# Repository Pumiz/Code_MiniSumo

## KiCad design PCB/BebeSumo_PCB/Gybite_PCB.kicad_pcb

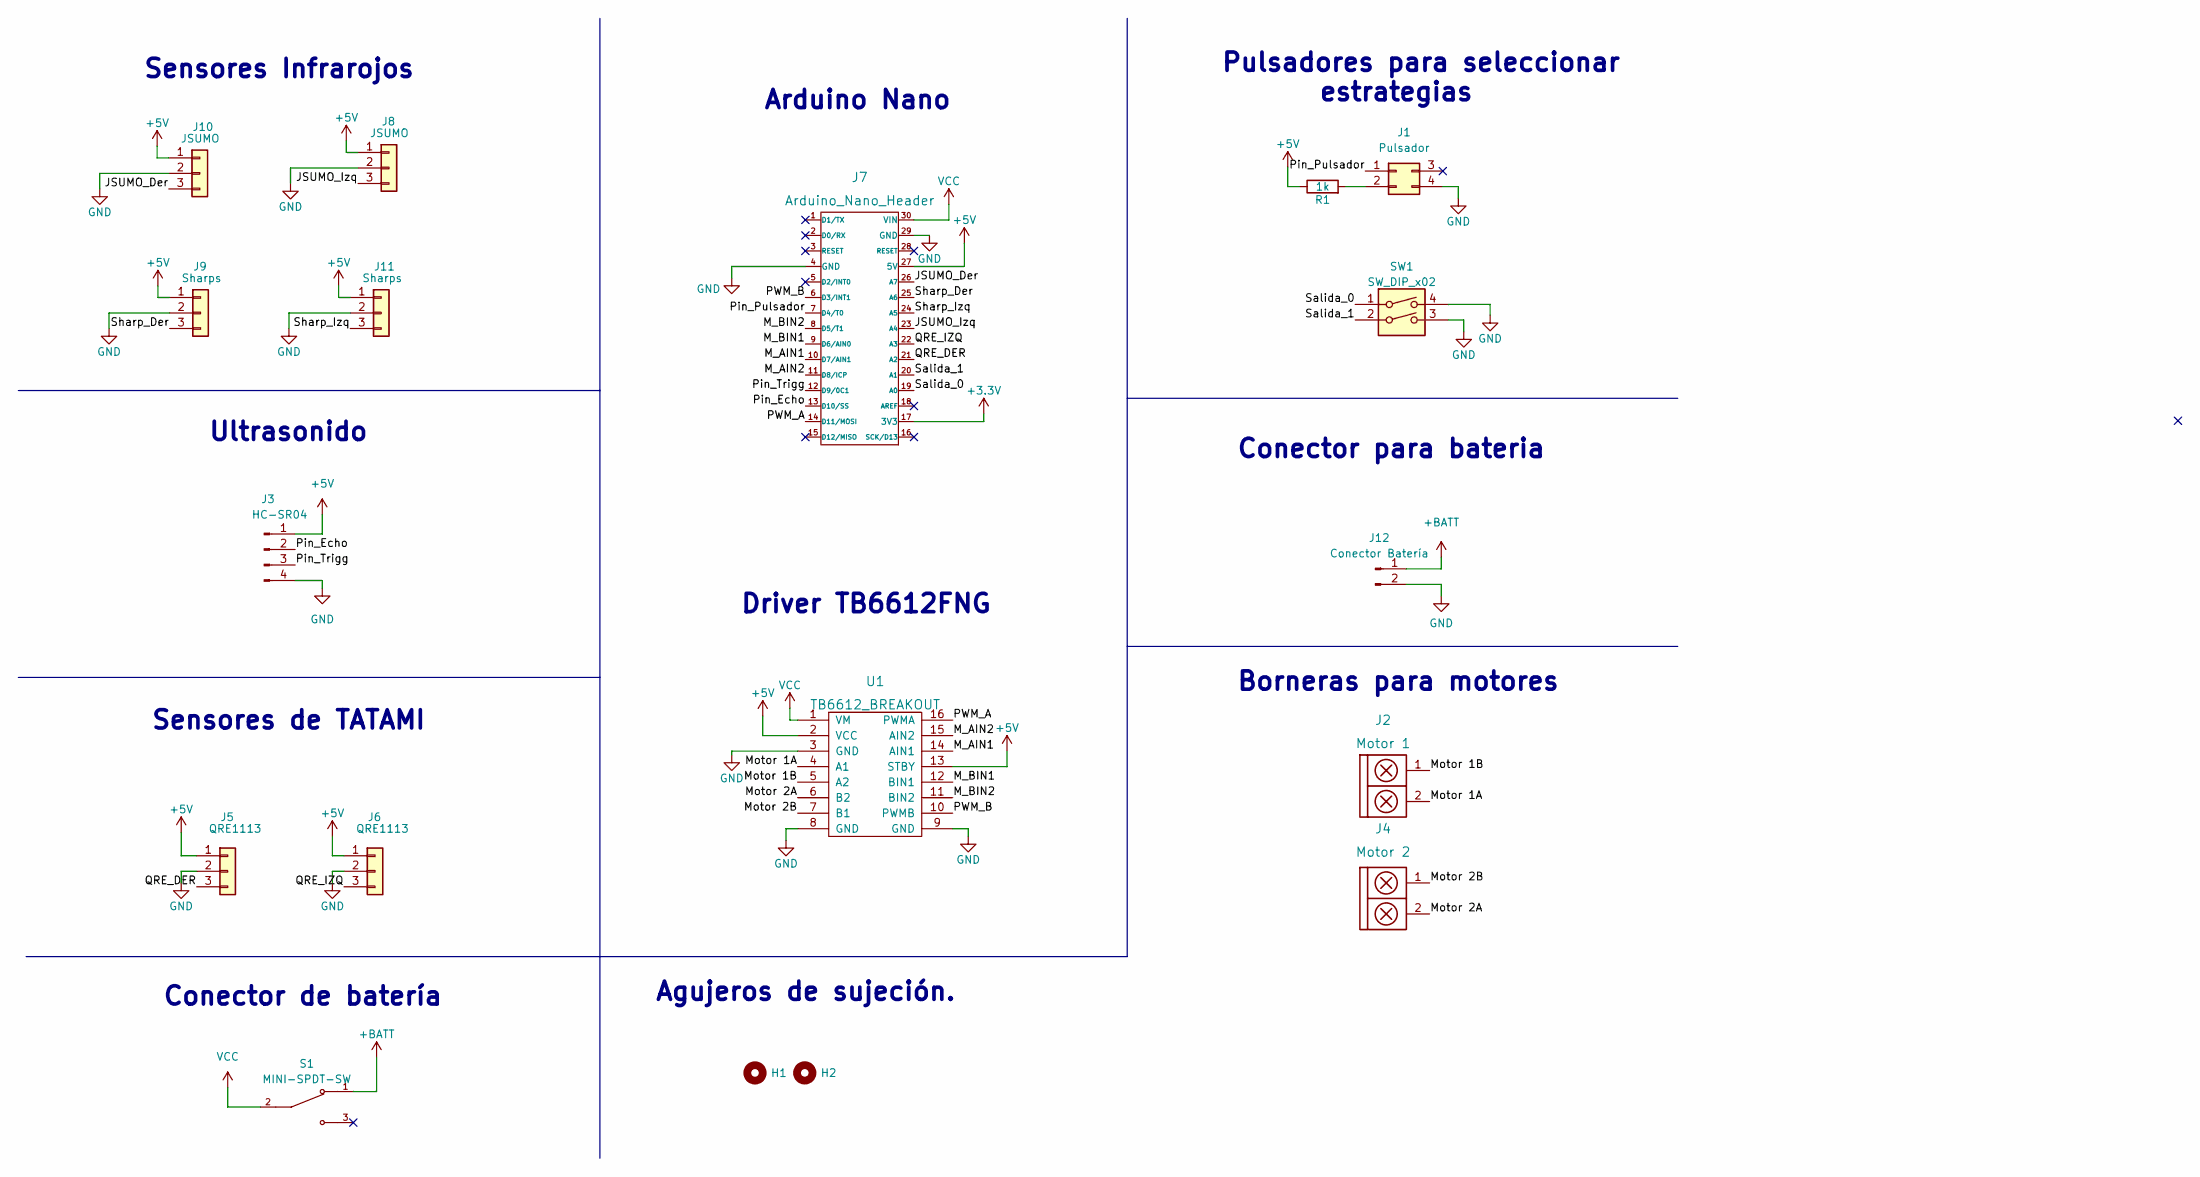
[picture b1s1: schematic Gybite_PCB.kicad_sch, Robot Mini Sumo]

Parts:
H1, H2: Mounting_Hole; hole_2mm
J1: Pulsador; Pulsador_TH_4
J2: Motor 1; BORNERA2_AZUL
J3: HC-SR04; JST_EH_B4B-EH-A_1x04_P2.50mm_Vertical
J4: Motor 2; BORNERA2_AZUL
J5, J6: QRE1113; JST_EH_B3B-EH-A_1x03_P2.50mm_Vertical
J7: Arduino_Nano_Header; arduino_nano_header
J8, J10: JSUMO; JST_EH_B3B-EH-A_1x03_P2.50mm_Vertical
J9, J11: Sharps; JST_EH_B3B-EH-A_1x03_P2.50mm_Vertical
J12: Conector Batería; JST_EH_B2B-EH-A_1x02_P2.50mm_Vertical
R1: 1k; RES0.3
S1: MINI-SPDT-SW; Switch_SS12F44_123; PARTREV C
SW1: SW_DIP_x02; SW_DIP_SPSTx02_Slide_9.78x7.26mm_W7.62mm_P2.54mm
U1: TB6612_BREAKOUT; TB6612_Breakout

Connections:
+3V3: J7.17 (3V3)
+5V: J3.1, J5.1, J6.1, J7.27 (5V), J8.1, J9.1, J10.1, J11.1, R1.1, U1.2 (VCC), U1.13 (STBY)
+BATT: J12.1, S1.1
/JSUMO_Der: J7.26 (A7), J10.3
/JSUMO_Izq: J7.23 (A4), J8.3
/M_AIN1: J7.10 (D7/AIN1), U1.14 (AIN1)
/M_AIN2: J7.11 (D8/ICP), U1.15 (AIN2)
/M_BIN1: J7.9 (D6/AIN0), U1.12 (BIN1)
/M_BIN2: J7.8 (D5/T1), U1.11 (BIN2)
/Motor 1A: J2.2, U1.4 (A1)
/Motor 1B: J2.1, U1.5 (A2)
/Motor 2A: J4.2, U1.6 (B2)
/Motor 2B: J4.1, U1.7 (B1)
/PWM_A: J7.14 (D11/MOSI), U1.16 (PWMA)
/PWM_B: J7.6 (D3/INT1), U1.10 (PWMB)
/Pin_Echo: J3.2, J7.13 (D10/SS)
/Pin_Pulsador: J1.1, J7.7 (D4/T0)
/Pin_Trigg: J3.3, J7.12 (D9/0C1)
/QRE_DER: J5.3, J7.21 (A2)
/QRE_IZQ: J6.3, J7.22 (A3)
/Salida_0: J7.19 (A0), SW1.1
/Salida_1: J7.20 (A1), SW1.2
/Sharp_Der: J7.25 (A6), J9.3
/Sharp_Izq: J7.24 (A5), J11.3
GND: J1.4, J3.4, J5.2, J6.2, J7.4 (GND), J7.29 (GND), J8.2, J9.2, J10.2, J11.2, J12.2, SW1.3, SW1.4, U1.3 (GND), U1.8 (GND), U1.9 (GND)
unnamed: J1.2, R1.2
VCC: J7.30 (VIN), S1.2, U1.1 (VM)

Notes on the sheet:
Borneras para motores
Driver TB6612FNG
Sensores Infrarojos
Conector de batería
Sensores de TATAMI
Arduino Nano
Agujeros de sujeción.
Pulsadores para seleccionar estrategias
Conector para bateria
Ultrasonido

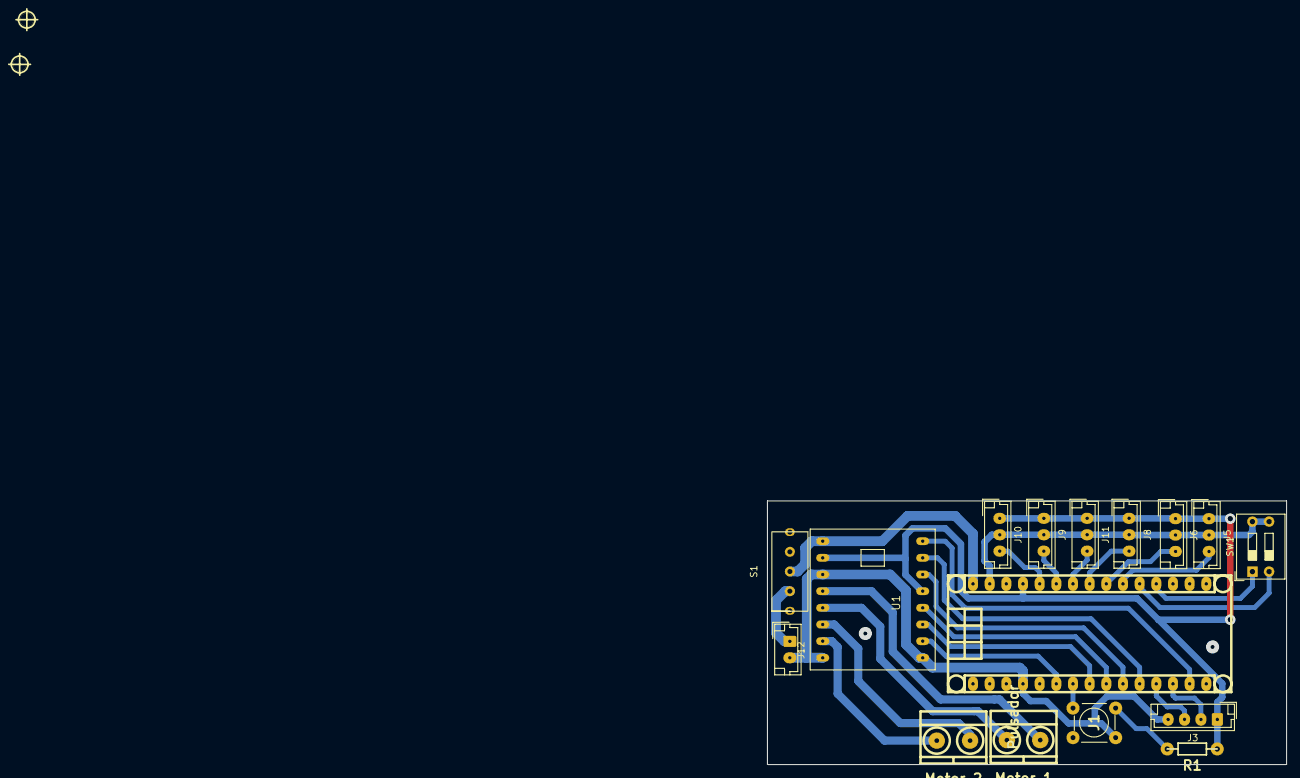
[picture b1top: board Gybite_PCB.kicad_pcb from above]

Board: 2 copper layers, 79.1 x 40.2 mm, 18 parts (0 on the bottom side), 26 nets.

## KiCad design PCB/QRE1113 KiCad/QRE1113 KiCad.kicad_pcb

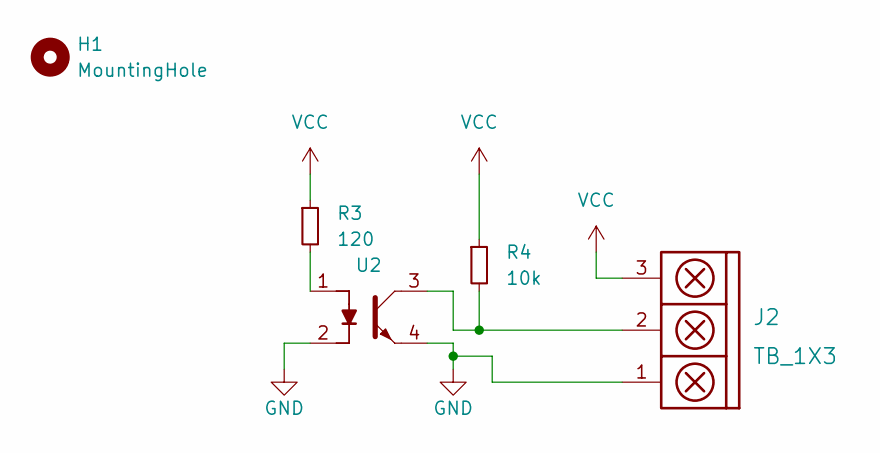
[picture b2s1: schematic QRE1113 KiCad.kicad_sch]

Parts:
H1: MountingHole; MountingHole_3.2mm_M3_DIN965_Pad
J2: TB_1X3; Pin_Strip_3
R3: 120; R_1206
R4: 10k; R_1206
U2: QRE1113; QRE1113GR

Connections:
GND: J2.1, U2.2, U2.4
unnamed: J2.2, R4.2, U2.3
unnamed: R3.2, U2.1
VCC: J2.3, R3.1, R4.1

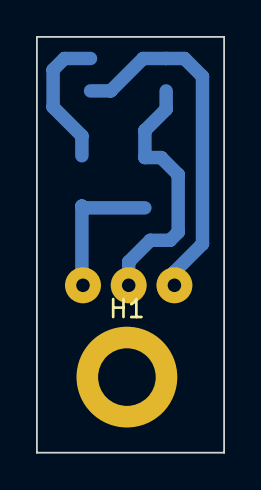
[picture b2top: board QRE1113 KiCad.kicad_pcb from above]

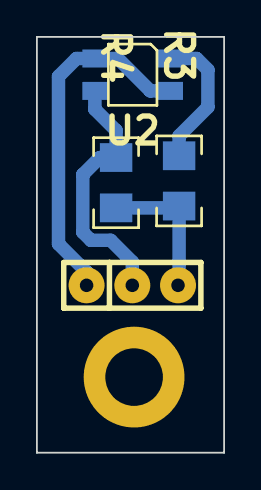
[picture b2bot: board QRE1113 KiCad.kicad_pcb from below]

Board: 2 copper layers, 10.4 x 23.1 mm, 5 parts (4 on the bottom side), 4 nets.

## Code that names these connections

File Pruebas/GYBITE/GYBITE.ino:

//--------------FUNCIONES GLOBALES---------------
#define DEBUG 1  //con DEBUG en 0 no muestra SerialPrint´s  
#define DEBUG_PULSADOR 1
#define DEBUG_CASOS 0
#define ON HIGH
#define OFF LOW
#include "Define.h"
#include "OnlyWrite.h"


//-------------------MOTORES---------------------
int Pines_Motor[6] = {
  MOTOR_DER_1,
  MOTOR_DER_2,
  MOTOR_IZQ_1,
  MOTOR_IZQ_2,
  PWM_MOTOR_DER,
  PWM_MOTOR_IZQ
};

//-------------------PULSADOR-------------------
enum Modo {
  Limpiar_Ruedas,
  Matar_Derecha,
  Te_Espero,
  Matar
};

String ESTADOS[] = {
  "Limpiar_Ruedas",
  "Matar_Derecha",
  "Te_Espero",
  "Matar",
};

//------------------ULTRASONIDO------------------
// MARRON:  VCC
// AZUL:    TRIG
// VERDE:   ECHO
// NEGRO:   GND

long Tiempo;
long Distancia;

//--------------------SHARP`S--------------------
// ROSA:     SEÑAL
// AMARILLO: GND
// CELESTE:  VCC

unsigned int SHARP_der = 0;
unsigned int SHARP_izq = 0;
unsigned int RivalSharp = 60;  // 60cm, basicamente al otra punta de tatami.

int Pines_Sharps[2] = {
  PIN_SHARP_DER,
  PIN_SHARP_IZQ,
};

//----------------------JSUMO--------------------
// ROSA:     SEÑAL
// AMARILLO: GND
// CELESTE:  VCC

int sensor = 0;

unsigned int JSUMO_der = 0;
unsigned int JSUMO_izq = 0;
unsigned int Rival = 500;  // Si no ve nada tira 0 o tende a valores muy cercados. Ej: 17
// Si detecta algo, NO IMPORTA LA DISTANCIA tende a arriba de los 800.

int Pines_JSUMO[2] = {
  PIN_JSUMO_F_D,
  PIN_JSUMO_F_I,
};

//---------------------QRE1113--------------------
//Próximamente.


//--------------------FUNCIONES-------------------

void AsignacionPines() {
  for (int idx = 0; idx < 6; idx++) {
    int pin = Pines_Motor[idx];
    pinMode(pin, OUTPUT);
  }

  for (int idx = 0; idx < 2; idx++) {
    int pin = Pines_Sharps[idx];
    pinMode(pin, INPUT);
  }

  for (int idx = 0; idx < 2; idx++) {
    int pin = Pines_JSUMO[idx];
    pinMode(pin, INPUT);
  }

  pinMode(PIN_PULSADOR, INPUT);
  pinMode(PIN_LED, OUTPUT);
  pinMode(PIN_ECHO, INPUT);
  pinMode(PIN_TRIG, OUTPUT);
  digitalWrite(PIN_TRIG, LOW);
}

void EnviarPulso() {
  digitalWrite(PIN_TRIG, HIGH);
  delayMicroseconds(10);
  digitalWrite(PIN_TRIG, LOW);
  Tiempo = pulseIn(PIN_ECHO, HIGH);
  Distancia = Tiempo / 58;  // El tiempo dividido 58 te da la distancia en centìmetros.
}

void SensarSensores() {

  JSUMO_izq = analogRead(PIN_JSUMO_F_I);
  JSUMO_der = analogRead(PIN_JSUMO_F_D);
  QREder = analogRead(QRE_DERECHO);
  QREizq = analogRead(QRE_IZQUIERDO);
}

void Menu() {
  while (!digitalRead(PIN_PULSADOR)) {
    tiempo++;
    Serial.println(tiempo);
  }
  if (tiempo > tiempo_min && tiempo < tiempo_max) {
    //cambiar estrategia
    caso++;
    tiempo = 0;
    if(DEBUG_PULSADOR)Serial.print("Estas en: ");
    if(DEBUG_PULSADOR)Serial.println(ESTADOS[caso]);
    pantalla = true;
  } else if (tiempo > tiempo_max && pantalla == true) {
    //entrar en el modo
    if(DEBUG_PULSADOR)Serial.print("En ruedo: ");
    if(DEBUG_PULSADOR)Serial.println(ESTADOS[caso]);
    digitalWrite(PIN_LED, HIGH);
    delay(5000);
    digitalWrite(PIN_LED, LOW);
    pantalla = false;
    Mode = true;
    tiempo = 0;
  }
}
#include "Estrategias.h"
//--------------------SETUP-------------------
void setup() {
  Serial.begin(9600);
  AsignacionPines();
  if(DEBUG_PULSADOR)Serial.print("Estas en: ");
  if(DEBUG_PULSADOR)Serial.println(ESTADOS[caso]);
  EncenderLed(); //esto es para saber cuando el arduino termino de leer las líneras anteriores a estas.
}

//--------------------LOOP-------------------
void loop() {

  Menu();


  switch (caso) {
    case Limpiar_Ruedas:
      if (Mode == true) {
        if(DEBUG_CASOS)Serial.println("EN RUEDO Limpiar Ruedas");
        LimpiarRuedas();
      }
      break;
    case Matar_Derecha:
      if (Mode == true) {
        if(DEBUG_CASOS)Serial.println("EN RUEDO Matar Derecha");
        MATARDERECHA();
      }
      break;
    case Te_Espero:
      if (Mode == true) {
        if(DEBUG_CASOS)Serial.println("EN RUEDO Te Espero...");
        TeEspero();
      }
      break;
    case Matar:
      if (Mode == true) {
        if(DEBUG_CASOS)Serial.println("EN RUEDO Matar");
        MATAR();
      }
      break;
  }
}

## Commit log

2022-09-07 Subo el codigo de FRAMAR
2022-09-14 Agregue el código del pulsador final del July
2022-09-14 Agregue el codigo base de Gybite
2022-09-22 Update Gybite_Code.ino
    Agregue todos los pines.
2022-09-27 Agregue el código del pulsador
2022-10-22 Update Gybite_Code.ino
    Actualice el codigo de Gybite para la fecha de La Salle. Estrategia uno funciona.
2022-11-02 Cambie el pulsador al pin digital.
2022-11-03 Agregue el codigod e Gybite optimizado
2022-11-09 Subo el codigo base con todas sus librerias nuevas.
2022-11-29 Agregue el nuevo pulsador y meti todas las librerias juntas.
2023-02-07 Nuevo codigo BebeSumo 2023
2023-04-12 Se agrego la carpeta con el PCB de la placa y los QRE
2023-04-14 Agregue nueva prueba de sharps
2023-04-17 Agregue debug a las acciones dentro de las estrategias.
2023-05-12 Se modifico la lectura del Sharp. Ahora funciona
2023-06-19 Agregue las nuevas estrategias: IZQ y DER
2023-06-20 Agregue las nuevas estrategias y correccion de errores.
2023-06-21 Codigo para probar el funcionamiento del QRE1113
2023-06-21 Se incorporo el calculo de los Sharps y nuevo codigo con nueva estrategia.
2023-06-21 Estrategias nueva y arregladas
2023-06-21 Nuevas constantes.
2023-06-21 Nueva funcion para mover motores.
2023-06-22 Nueva actualización general
2023-06-22 Cree una nueva constante de velocidad
2023-06-22 Se arreglo la libreria que detecta errores
2023-06-22 Se crearon nuevas estrategias de derecha e izquierda
2023-06-22 Se creó un nuevo movimiento de los motores
2023-06-22 Código para testear sensor QRE1113
2023-06-23 Se corriguieron errores del UltraSonido
2023-06-23 Se agregaron nuevos bools y nuevas velocidades de ruedas
2023-07-20 Se vació el loop y se reestructuro el codigo
2023-07-28 Seagregaron las carpetas para Vs Code
2023-07-29 Nuevos booleanos y detalles
2023-07-29 Ajuste de velocidad a motores de ataque rápido
2023-07-29 Se arreglaron las 3 estrategias.
2023-07-29 Codigo arreglado utilizado en ITBA 29/7/23
2023-07-30 Ahroa al limpiar ruedas no hay que esperar los 5 segundos
2023-10-04 Agregue un codigo de pruebas para testear el la velocidad y sentido de giro de los motores JSUMO
2023-10-05 Se cambiaron los pines del motor derecho y se solucionaron errores
2023-10-05 Se cambiaron los valores de velocidades para los nuevos motores
2023-10-05 Se arreglo la logica de las funciones, ahora cada una corresponde a cada motor con su moviemiento
2023-10-05 Se eliminaron lineas al pedo y se corriguieron errores
2023-10-06 Codigo para rampear los motores
2023-10-10 Se cambio el valor de la linea blanca, se cambiaron las condiciones del for para configuarar los pines
2023-10-10 Elimine variables que no se usaban
2023-10-10 Ahora se llama a la libreria del sharp dentro Estrategias
2023-10-27 Cree una libreria para los motores
2023-10-27 Cree una libreria para obtener la distancia de los sharps
2023-10-27 Instancie los motores y los sharps, Se arreglaron errores y ahora se llama a una unica estretegia independientemente del lado para el que busque
2023-10-27 Cree un codigo para probar los sensores JSUMO con la lectura de sus valores
2023-10-27 Codigo para probar los motores indivualmente
2023-10-27 Subo codigo para probar los QRE, tanto la lectura como tambien el movimeinto de cuando detecta la linea
2023-10-27 Se cambiaron los pines de los sensores y de los motores.
2023-10-27 Ahora hay una sola estrategia y un if determian para que lado busca, ademas los motores se los llama desde la libreria
2023-10-27 Nuevos cambios, librerias y arreglo de errores.
2023-10-30 Rediseño de la placa, ahora tiene un dip y la huella para el nuevo interruptor de corriente.
2023-11-08 Se cambio el valor de la velocidad al buscar.
2023-11-08 Ahora cuando busca lo hace en el lugar y se aumento el tiempo que retrocede cuando detecta linea.
2023-11-08 Nuevas varianbles para el DIP y su codigo para leerlo con la tabla de verdad.
